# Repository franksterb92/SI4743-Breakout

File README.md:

# SI4743-Breakout

Not much to say about this project so far...... but This is an All Band Radio Reciver Breakout Board Based off the SI4743 IC i will be updating this as time allows and writing 
stm32 drivers for this boad and as well after i accually get the boad manufactered i will desined the board to fit dierectly on a nucleo 64 board.

UPDATE 11/4/2022 i made the board in the nucleo formfactor and changed the crystal to a smd device and now the usb connector is hooked up to the morpho connectors.
!!!!!!!!!!!!!!!!!!!!!!WARNING THIS BOARD IS GOING THROUGH TESTING SO PROCEED AT YOUR OWN RISK!!!!!!!!!!!!!!!!!!!!!!!!!!!!!!!!!!!!

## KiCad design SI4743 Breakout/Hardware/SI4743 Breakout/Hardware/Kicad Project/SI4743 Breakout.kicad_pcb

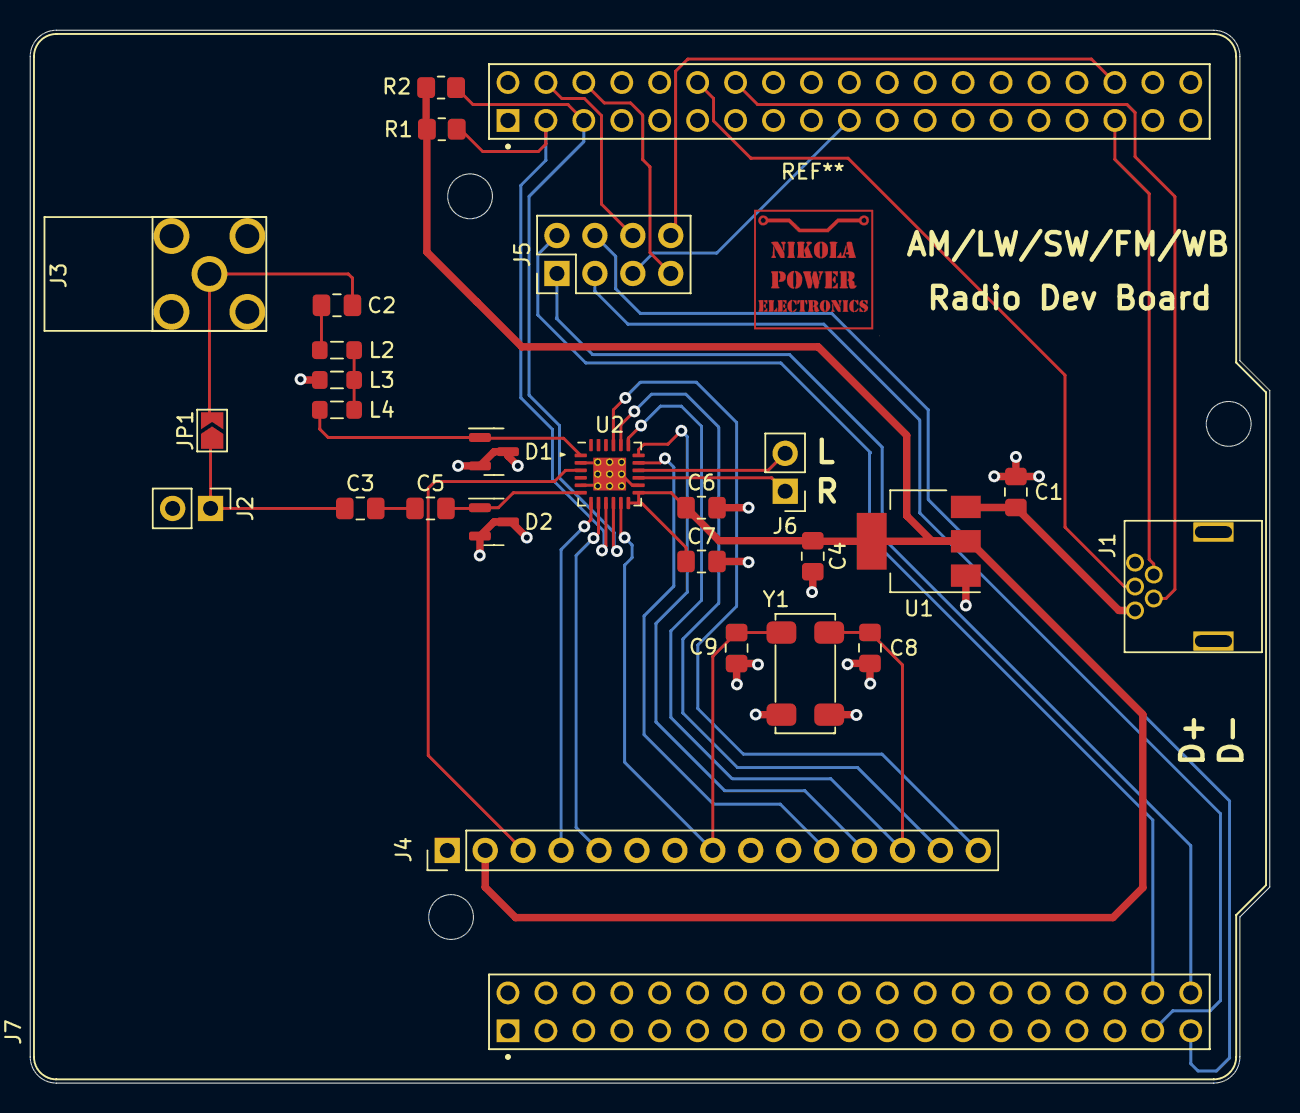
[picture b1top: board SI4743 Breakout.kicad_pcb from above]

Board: 4 copper layers, 83.0 x 70.5 mm, 27 parts (0 on the bottom side), 34 nets.

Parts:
C1, C4, C6, C7: 100uf; C_0805_2012Metric_Pad1.18x1.45mm_HandSolder
C2, C8, C9: 18pf; C_0805_2012Metric_Pad1.18x1.45mm_HandSolder
C3: 33pf; C_0805_2012Metric_Pad1.18x1.45mm_HandSolder
C5: 470nf; C_0805_2012Metric_Pad1.18x1.45mm_HandSolder
D1, D2: CM1213A-01SO; SOT-23
J1: USB_B_Mini; 54-00019
J2: AM ANT; PinHeader_1x02_P2.54mm_Vertical
J3: FM Ant.; 0731000114
J4: Interface Conn; PinHeader_1x15_P2.54mm_Vertical
J5: Conn_02x04_Counter_Clockwise; PinHeader_2x04_P2.54mm_Vertical
J6: Analog Audio; PinHeader_1x02_P2.54mm_Vertical
J7: F446RE_Morpho; Nucleo-64 Without Arduino Header
JP1: SolderJumper_2_Open; SolderJumper-2_P1.3mm_Open_TrianglePad1.0x1.5mm
L2: 100nh; L_0805_2012Metric_Pad1.05x1.20mm_HandSolder
L3: 120nh; L_0805_2012Metric_Pad1.05x1.20mm_HandSolder
L4: 150nh; L_0805_2012Metric_Pad1.05x1.20mm_HandSolder
R1, R2: 2K2; R_0805_2012Metric_Pad1.20x1.40mm_HandSolder
U1: AMS1117-3.3; SOT-223-3_TabPin2
U2: SI4743; SI474x
Y1: 32.768KHZ; RSM200S-32.768-12.5-TR

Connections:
AGC: J4.3, U2.3 (AGC1)
AGC2: J4.15, U2.21 (GPO1/AGC2)
AMI: C5.2, D2.1 (CH1), U2.6 (AMI)
DCLK: C8.1, J4.13, U2.19 (GPO3/DCLK), Y1.4
DFS: J4.12, U2.18 (DFS)
DOUT: J4.11, U2.17 (DOUT)
FMI: D1.1 (CH1), L4.2, U2.1 (FMI)
GND: C1.2, C4.2, C6.2, C7.2, C8.2, C9.2, D1.2 (VP), D1.3 (VN), D2.2 (VP), D2.3 (VN), J1.5 (GND), J1.6 (Shield), J2.2, J3.2 (Ext), J4.1, L3.2, U1.1 (GND), U2.2 (RFGND), U2.5 (GND), U2.14 (GND), U2.25 (GND), Y1.2, Y1.3
INT: J4.14, U2.20 (GPO2/~INT)
LOUT: J6.2, U2.16 (LOUT)
unnamed: C1.1, J1.1 (VBUS), U1.3 (VI)
unnamed: C2.1, J3.1 (In), JP1.2 (B)
unnamed: C2.2, L2.1
unnamed: C3.1, J2.1, JP1.1 (A)
unnamed: C3.2, C5.1
unnamed: L2.2, L3.1, L4.1
PC0: J5.1, J7.38 (PC0)
PC1: J5.2, J7.36 (PC1)
PC2: J5.3, J7.35 (PC2)
PC3: J5.4, J7.37 (PC3)
PC4: J5.8, J7.72 (PC4)
PC5: J5.7, J7.44 (PC5)
PC6: J5.6, J7.42 (PC6)
PC7: J5.5, J7.57 (PC7)
RCLK: C9.1, J4.8, U2.11 (RCLK), Y1.1
ROUT: J6.1, U2.15 (ROUT)
RST: J4.4, U2.7 (~RST)
SCL: J7.41 (PB8), R1.2, U2.9 (SCLK)
SDA: J7.43 (PB9), R2.2, U2.10 (SDIO)
SEN: J4.5, U2.8 (~SEN)
USB D+: J1.3 (D+), J7.50 (PA12)
USB D-: J1.2 (D-), J7.52 (PA11)
USB ID: J1.4 (ID), J7.71 (PA10)
VDD: C4.1, C6.1, C7.1, J4.2, R1.1, R2.1, U1.2 (VO), U2.12 (VIO), U2.13 (VDD)
